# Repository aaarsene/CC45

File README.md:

# CC45

THIS IS A WORK IN PROGRESS

⚠️ **Switch spacing is 19mm** ⚠️

[Interactive BOM](http://htmlpreview.github.io/?https://github.com/aaarsene/CC45/blob/master/bom/ibom.html)

## Supported layouts

## PCB Render

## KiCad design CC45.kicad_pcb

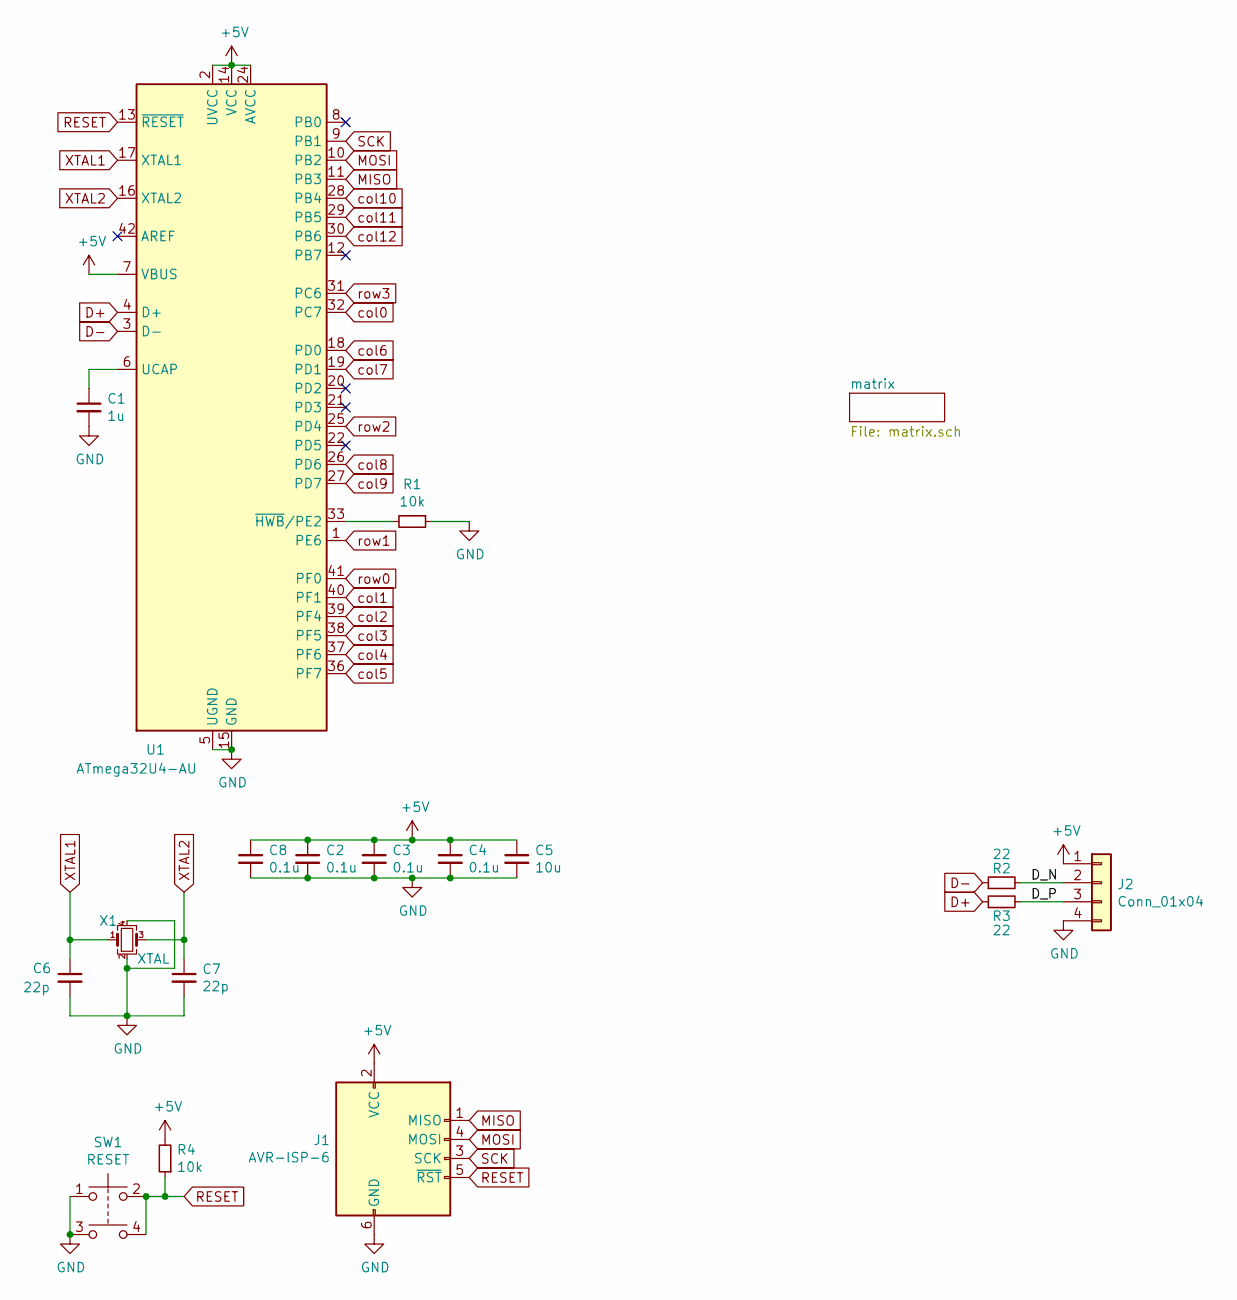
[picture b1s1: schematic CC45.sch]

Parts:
C1: 1u; C_1206_3216Metric_Pad1.42x1.75mm_HandSolder; LCSC C1848
C2, C3, C4, C8: 0.1u; C_1206_3216Metric_Pad1.42x1.75mm_HandSolder; LCSC C24497
C5: 10u; C_1206_3216Metric_Pad1.42x1.75mm_HandSolder; LCSC C13585
C6, C7: 22p; C_1206_3216Metric_Pad1.42x1.75mm_HandSolder; LCSC C313096
J1: AVR-ISP-6; Reset_Pretty-Mask
J2: Conn_01x04; JST-SR-4
R1, R4: 10k; R_1206_3216Metric_Pad1.42x1.75mm_HandSolder; LCSC C17902
R2, R3: 22; R_1206_3216Metric_Pad1.42x1.75mm_HandSolder; LCSC C17958
SW1: RESET; SKQG-1155865; LCSC C318884
U1: ATmega32U4-AU; TQFP-44_10x10mm_P0.8mm; LCSC C44854
X1: XTAL; Crystal_SMD_3225-4Pin_3.2x2.5mm_HandSoldering; LCSC C13738

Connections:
+5V: C2.1, C3.1, C4.1, C5.1, C8.1, J1.2 (VCC), J2.1, R4.2, U1.2 (UVCC), U1.7 (VBUS), U1.14 (VCC), U1.24 (AVCC), U1.34 (VCC), U1.44 (AVCC)
/D_N: J2.2, R2.2
/D_P: J2.3, R3.2
D+: R3.1, U1.4 (D+)
D-: R2.1, U1.3 (D-)
GND: C1.2, C2.2, C3.2, C4.2, C5.2, C6.2, C7.2, C8.2, J1.6 (GND), J2.4, R1.1, SW1.1, SW1.3, U1.5 (UGND), U1.15 (GND), U1.23 (GND), U1.35 (GND), U1.43 (GND), X1.2, X1.4
MISO: J1.1 (MISO), U1.11 (PB3)
MOSI: J1.4 (MOSI), U1.10 (PB2)
unnamed: C1.1, U1.6 (UCAP)
unnamed: R1.2, U1.33 (~HWB~/PE2)
RESET: J1.5 (~RST), R4.1, SW1.2, SW1.4, U1.13 (~RESET)
SCK: J1.3 (SCK), U1.9 (PB1)
XTAL1: C6.1, U1.17 (XTAL1), X1.1
XTAL2: C7.1, U1.16 (XTAL2), X1.3
col0: U1.32 (PC7); also elsewhere on the board
col1: U1.40 (PF1); also elsewhere on the board
col2: U1.39 (PF4); also elsewhere on the board
col3: U1.38 (PF5); also elsewhere on the board
col4: U1.37 (PF6); also elsewhere on the board
col5: U1.36 (PF7); also elsewhere on the board
col6: U1.18 (PD0); also elsewhere on the board
col7: U1.19 (PD1); also elsewhere on the board
col8: U1.26 (PD6); also elsewhere on the board
col9: U1.27 (PD7); also elsewhere on the board
col10: U1.28 (PB4); also elsewhere on the board
col11: U1.29 (PB5); also elsewhere on the board
col12: U1.30 (PB6); also elsewhere on the board
row0: U1.41 (PF0); also elsewhere on the board
row1: U1.1 (PE6); also elsewhere on the board
row2: U1.25 (PD4); also elsewhere on the board
row3: U1.31 (PC6); also elsewhere on the board

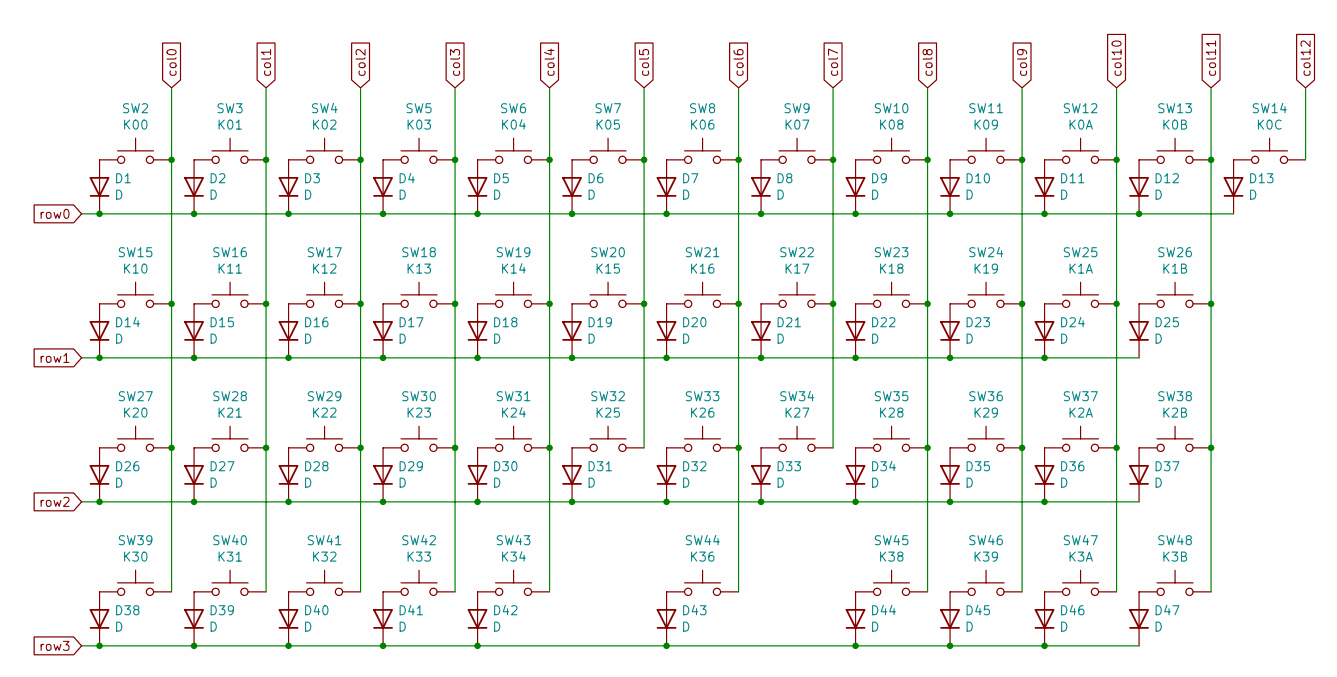
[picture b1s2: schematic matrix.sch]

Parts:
D1, D2, D3, D4, D5, D6, D7, D8, D9, D10, D11, D12, D13, D14, D15, D16, D17, D18, D19, D20, D21, D22, D23, D24, D25, D26, D27, D28, D29, D30, D31, D32, D33, D34, D35, D36, D37, D38, D39, D40, D41, D42, D43, D44, D45, D46, D47: D; D_SOD-323_HandSoldering; LCSC C84063
SW2: K00; MX_19mm-1U-NoLED
SW3: K01; MX_19mm-1U-NoLED
SW4: K02; MX_19mm-1U-NoLED
SW5: K03; MX_19mm-1U-NoLED
SW6: K04; MX_19mm-1U-NoLED
SW7: K05; MX_19mm-1U-NoLED
SW8: K06; MX_19mm-1U-NoLED
SW9: K07; MX_19mm-1U-NoLED
SW10: K08; MX_19mm-1U-NoLED
SW11: K09; MX_19mm-1U-NoLED
SW12: K0A; MX_19mm-1U-NoLED
SW13: K0B; MX_19mm-1U-NoLED
SW14: K0C; MX_19mm-1U-NoLED
SW15: K10; MX_19mm-1.25U-NoLED
SW16: K11; MX_19mm-1U-NoLED
SW17: K12; MX_19mm-1U-NoLED
SW18: K13; MX_19mm-1U-NoLED
SW19: K14; MX_19mm-1U-NoLED
SW20: K15; MX_19mm-1U-NoLED
SW21: K16; MX_19mm-1U-NoLED
SW22: K17; MX_19mm-1U-NoLED
SW23: K18; MX_19mm-1U-NoLED
SW24: K19; MX_19mm-1U-NoLED
SW25: K1A; MX_19mm-1U-NoLED
SW26: K1B; MX_19mm-1.75U-NoLED
SW27: K20; MX_19mm-1.75U-NoLED
SW28: K21; MX_19mm-1U-NoLED
SW29: K22; MX_19mm-1U-NoLED
SW30: K23; MX_19mm-1U-NoLED
SW31: K24; MX_19mm-1U-NoLED
SW32: K25; MX_19mm-1U-NoLED
SW33: K26; MX_19mm-1U-NoLED
SW34: K27; MX_19mm-1U-NoLED
SW35: K28; MX_19mm-1U-NoLED
SW36: K29; MX_19mm-1U-NoLED
SW37: K2A; MX_19mm-1U-NoLED
SW38: K2B; MX_19mm-1.25U-NoLED
SW39: K30; MX_19mm-1.25U-NoLED
SW40: K31; MX_19mm-1U-NoLED
SW41: K32; MX_19mm-1.25U-NoLED
SW42: K33; MX_19mm-1.25U-NoLED
SW43: K34; MX_19mm-1.75U-NoLED
SW44: K36; MX_19mm-1.75U-NoLED
SW45: K38; MX_19mm-1.25U-NoLED
SW46: K39; MX_19mm-1.25U-NoLED
SW47: K3A; MX_19mm-1U-NoLED
SW48: K3B; MX_19mm-1.25U-NoLED

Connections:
unnamed: D1.2 (A), SW2.1
unnamed: D2.2 (A), SW3.1
unnamed: D3.2 (A), SW4.1
unnamed: D4.2 (A), SW5.1
unnamed: D5.2 (A), SW6.1
unnamed: D6.2 (A), SW7.1
unnamed: D7.2 (A), SW8.1
unnamed: D8.2 (A), SW9.1
unnamed: D9.2 (A), SW10.1
unnamed: D10.2 (A), SW11.1
unnamed: D11.2 (A), SW12.1
unnamed: D12.2 (A), SW13.1
unnamed: D13.2 (A), SW14.1
unnamed: D14.2 (A), SW15.1
unnamed: D15.2 (A), SW16.1
unnamed: D16.2 (A), SW17.1
unnamed: D17.2 (A), SW18.1
unnamed: D18.2 (A), SW19.1
unnamed: D19.2 (A), SW20.1
unnamed: D20.2 (A), SW21.1
unnamed: D21.2 (A), SW22.1
unnamed: D22.2 (A), SW23.1
unnamed: D23.2 (A), SW24.1
unnamed: D24.2 (A), SW25.1
unnamed: D25.2 (A), SW26.1
unnamed: D26.2 (A), SW27.1
unnamed: D27.2 (A), SW28.1
unnamed: D28.2 (A), SW29.1
unnamed: D29.2 (A), SW30.1
unnamed: D30.2 (A), SW31.1
unnamed: D31.2 (A), SW32.1
unnamed: D32.2 (A), SW33.1
unnamed: D33.2 (A), SW34.1
unnamed: D34.2 (A), SW35.1
unnamed: D35.2 (A), SW36.1
unnamed: D36.2 (A), SW37.1
unnamed: D37.2 (A), SW38.1
unnamed 46: D38.2 (A), SW39.1; also elsewhere on the board
unnamed 47: D39.2 (A), SW40.1; also elsewhere on the board
unnamed: D40.2 (A), SW41.1
unnamed 49: D41.2 (A), SW42.1; also elsewhere on the board
unnamed 50: D42.2 (A), SW43.1; also elsewhere on the board
unnamed: D43.2 (A), SW44.1
unnamed 52: D44.2 (A), SW45.1; also elsewhere on the board
unnamed: D45.2 (A), SW46.1
unnamed 54: D46.2 (A), SW47.1; also elsewhere on the board
unnamed 55: D47.2 (A), SW48.1; also elsewhere on the board
col0: SW2.2, SW15.2, SW27.2, SW39.2; also elsewhere on the board
col1: SW3.2, SW16.2, SW28.2, SW40.2; also elsewhere on the board
col2: SW4.2, SW17.2, SW29.2, SW41.2; also elsewhere on the board
col3: SW5.2, SW18.2, SW30.2, SW42.2; also elsewhere on the board
col4: SW6.2, SW19.2, SW31.2, SW43.2; also elsewhere on the board
col5: SW7.2, SW20.2, SW32.2; also elsewhere on the board
col6: SW8.2, SW21.2, SW33.2, SW44.2; also elsewhere on the board
col7: SW9.2, SW22.2, SW34.2; also elsewhere on the board
col8: SW10.2, SW23.2, SW35.2, SW45.2; also elsewhere on the board
col9: SW11.2, SW24.2, SW36.2, SW46.2; also elsewhere on the board
col10: SW12.2, SW25.2, SW37.2, SW47.2; also elsewhere on the board
col11: SW13.2, SW26.2, SW38.2, SW48.2; also elsewhere on the board
col12: SW14.2; also elsewhere on the board
row0: D1.1 (K), D2.1 (K), D3.1 (K), D4.1 (K), D5.1 (K), D6.1 (K), D7.1 (K), D8.1 (K), D9.1 (K), D10.1 (K), D11.1 (K), D12.1 (K), D13.1 (K); also elsewhere on the board
row1: D14.1 (K), D15.1 (K), D16.1 (K), D17.1 (K), D18.1 (K), D19.1 (K), D20.1 (K), D21.1 (K), D22.1 (K), D23.1 (K), D24.1 (K), D25.1 (K); also elsewhere on the board
row2: D26.1 (K), D27.1 (K), D28.1 (K), D29.1 (K), D30.1 (K), D31.1 (K), D32.1 (K), D33.1 (K), D34.1 (K), D35.1 (K), D36.1 (K), D37.1 (K); also elsewhere on the board
row3: D38.1 (K), D39.1 (K), D40.1 (K), D41.1 (K), D42.1 (K), D43.1 (K), D44.1 (K), D45.1 (K), D46.1 (K), D47.1 (K); also elsewhere on the board

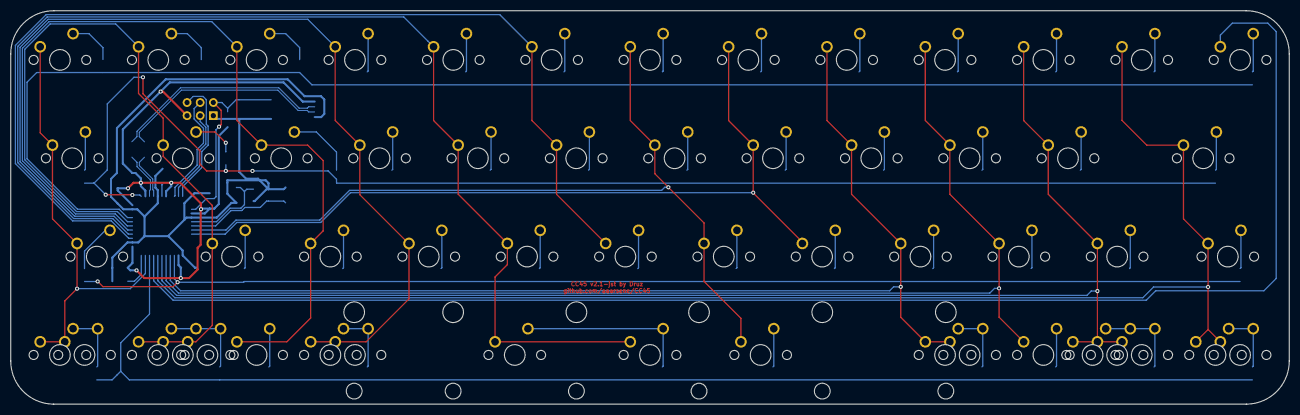
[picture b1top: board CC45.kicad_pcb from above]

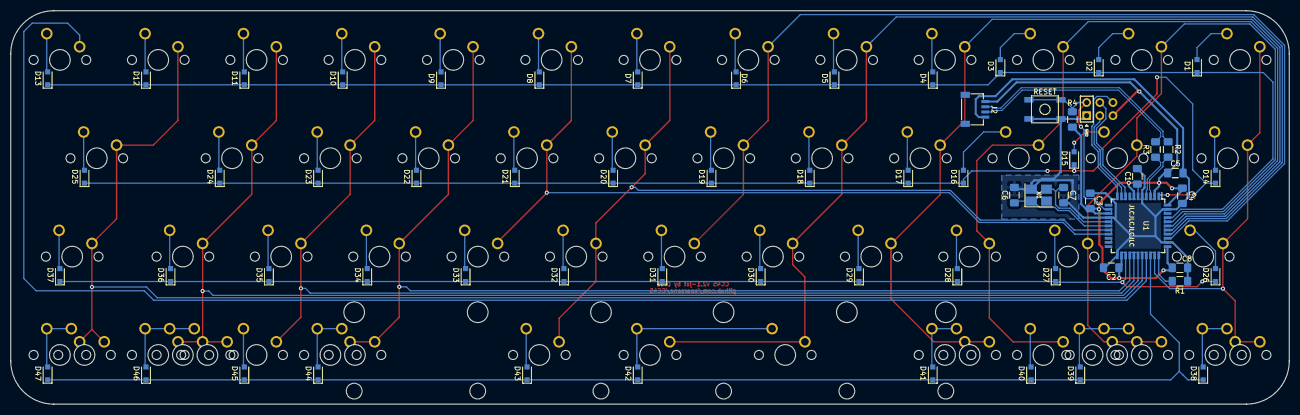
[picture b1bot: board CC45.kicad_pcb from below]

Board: 2 copper layers, 247.0 x 76.0 mm, 120 parts (64 on the bottom side), 78 nets.

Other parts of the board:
SW39#2: K30; MX_19mm-1U-NoLED
SW40#2, SW40#3: K31; MX_19mm-1U-NoLED
SW42#2: K33; MX_19mm-1U-NoLED
SW43#2: K34; MX_19mm-2.25U-ReversedStabilizers-NoLED
SW45#2: K38; MX_19mm-1U-NoLED
SW47#2, SW47#3: K3A; MX_19mm-1U-NoLED
SW48#2: K3B; MX_19mm-1U-NoLED

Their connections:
unnamed 46: SW39#2.1; also elsewhere on the board
unnamed 47: SW40#2.1, SW40#3.1; also elsewhere on the board
unnamed 49: SW42#2.1; also elsewhere on the board
unnamed 50: SW43#2.1; also elsewhere on the board
unnamed 52: SW45#2.1; also elsewhere on the board
unnamed 54: SW47#2.1, SW47#3.1; also elsewhere on the board
unnamed 55: SW48#2.1; also elsewhere on the board
col0: SW39#2.2; also elsewhere on the board
col1: SW40#2.2, SW40#3.2; also elsewhere on the board
col3: SW42#2.2; also elsewhere on the board
col4: SW43#2.2; also elsewhere on the board
col8: SW45#2.2; also elsewhere on the board
col10: SW47#2.2, SW47#3.2; also elsewhere on the board
col11: SW48#2.2; also elsewhere on the board

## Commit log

2020-06-15 Add gitignore
2020-06-15 Add submodules
2020-06-15 Add libraries to kicad project
2020-06-15 created mcu schematic
2020-06-15 add switch matrix and assign footprints
2020-06-16 changed switches footprint submodule
2020-06-16 Placed footprints on pcb and routed everything except the matrix
2020-06-16 rework components postion around the mcu and usb
2020-06-17 Connect matrix to mcu on the schema and moved some components around
2020-06-17 removed MX_Alps_Hybrid submodule
2020-06-17 Routed the matrix
2020-06-17 moved values on silkscreen to make them more visible
2020-06-18 modified the pcb file to be compatible with the latest stable release of kicad
2020-06-18 Add a decoupling capacitor
2020-06-18 Add fill zones
2020-06-19 Visual improvements, mostly on the silkscreen
2020-06-21 moving C4 closer to the mcu and adding JLC parts numbers
2020-06-21 moved the middle mounting point to the center of the pcb
2020-06-21 Added images to the readme
2020-06-21 Added gerber files
2020-07-02 added the 1u keys for the 1.5u bottom row option
2020-07-03 fix reset button wiring
2020-07-05 Updated version number on pcb
2020-07-05 removed gerber from source control
2020-11-07 v2 update
2020-12-27 Added interactive bom
2020-12-29 Update link to interactive bom
2021-01-06 Increased corner radius
2021-03-17 Changed layout image
2021-03-17 Updated layout image
2021-03-17 Updated version written on pcb
2021-05-07 Remove bottom corners switches for a traymount hhkb case
2021-06-15 Add warning about switch spacing
2021-09-17 Remove usb port and safeties, add jst connector
2021-09-24 Update step
2022-03-19 2022-03-19
